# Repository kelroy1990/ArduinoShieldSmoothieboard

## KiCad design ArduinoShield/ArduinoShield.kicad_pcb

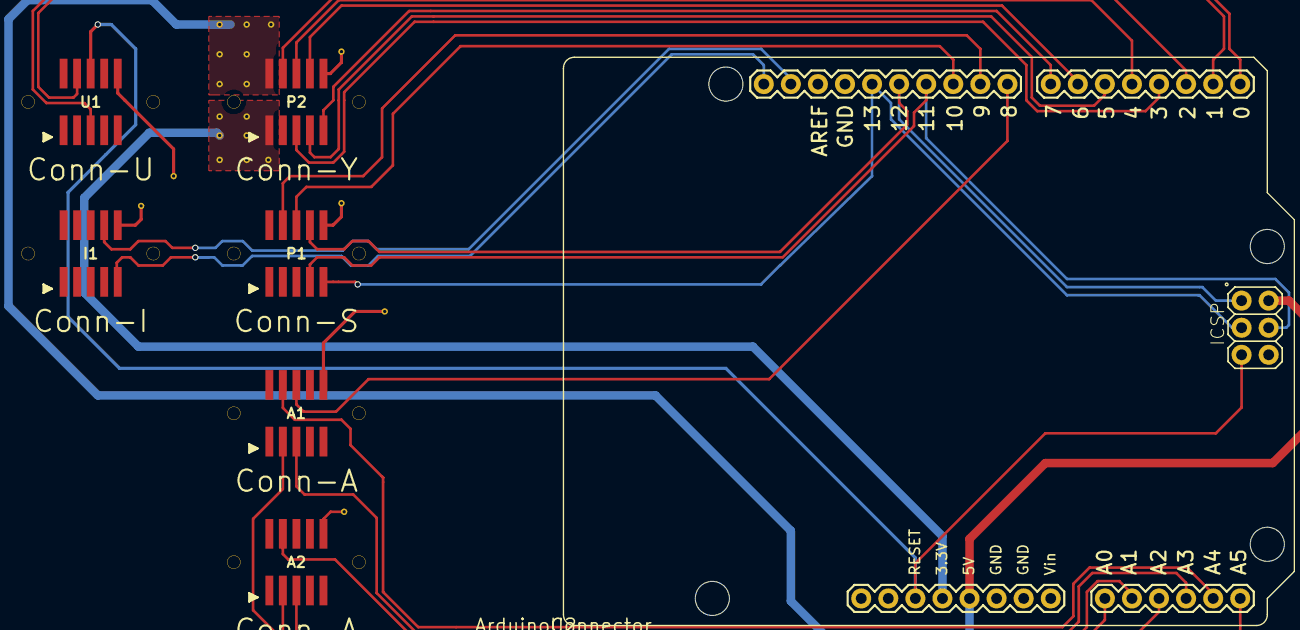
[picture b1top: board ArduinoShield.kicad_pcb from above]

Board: 2 copper layers, 7 parts (0 on the bottom side), 26 nets.

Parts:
A1, A2: Conn-A; SHF-105-01-L-D-SM-LC
I1: Conn-I; SHF-105-01-L-D-SM-LC
P1: Conn-S; SHF-105-01-L-D-SM-LC
P2: Conn-Y; SHF-105-01-L-D-SM-LC
U1: Conn-U; SHF-105-01-L-D-SM-LC
U2: ArduinoConnector; ARDUINO_UNO

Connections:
/3.3V: P2.1, U2.3.3V
/5V: P2.2, U2.5V
/A0: A2.5, U2.A0
/A1: A2.4, U2.A1
/A2: A2.3, U2.A2
/A3: A1.5, U2.A3
/A4: A1.4, U2.A4
/A5: A1.3, U2.A5
/G2: P2.4, U2.2
/G3: P2.5, U2.3
/G4: P2.6, U2.4
/G5: P2.7, U2.5
/G6: P2.8, U2.6
/G7: P2.9, U2.7
/G8: A1.6, U2.8
/G9: P1.4, U2.9
/MISO: P1.8, U2.12
/MOSI: P1.7, U2.11
/RESET: U1.6, U2.RESE
/RX: U1.5, U2.0
/SCK: P1.9, U2.13
/SCL: I1.9, U2.SCL
/SDA: I1.8, U2.SDA
/SS: P1.6, U2.10
/TX: U1.4, U2.1
GND: A1.10, A2.10, I1.10, P1.10, P2.10, U1.10, U2.GND

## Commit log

2017-04-27 First board Upload v1.0
2017-04-27 Fixed readme
